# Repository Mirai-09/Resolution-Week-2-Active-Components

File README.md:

# Resolution-Week-2-Active-Components
This is a circuit that I designed for Week 2 of Resolution Hardware
My circuit has LEDs that blink when a switch is pressed as well as turn on for a few seconds and then turn off.  

# How it works
This circuit has two Multivibrators in it. The one on the left is a Astable Multivibrator. It makes the LEDs on the left blink on and off when the switch is turned on. The one on the right is a Monostable Multivibrator. When the switch on the left is pressed and released, the LEDs turn on for a few seconds and then turn off. I have made thi circuit with the help of transistors, capcitors and resistors.

# Schematic 
Here is my schematic!  

# PCB
Here is my PCB design!    
Front:  
  
Back:  
  
3D front:

3D Back:

# Demo!
GIF :)  
  
Video Link:  
https://youtu.be/-CvgjkiQHqE  
Falstad Link:  
https://is.gd/h47ZDy

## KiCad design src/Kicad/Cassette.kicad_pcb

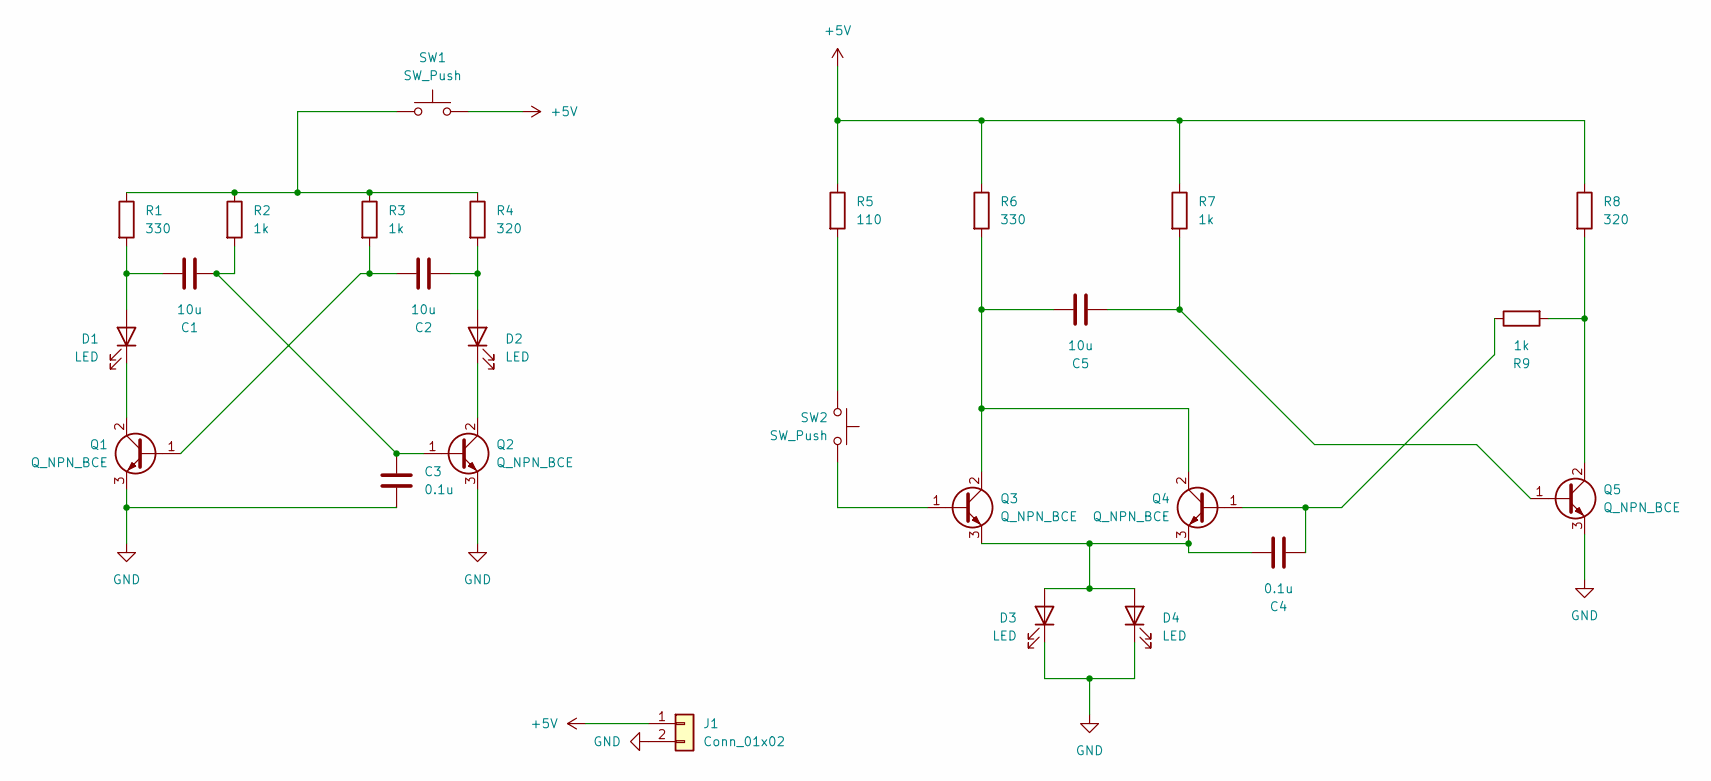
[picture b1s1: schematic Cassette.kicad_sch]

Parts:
C1, C2, C5: 10u; C_Disc_D5.0mm_W2.5mm_P5.00mm
C3, C4: 0.1u; C_Disc_D5.0mm_W2.5mm_P5.00mm
D1, D2, D3, D4: LED; LED_D5.0mm
J1: Conn_01x02; PinHeader_1x02_P2.54mm_Vertical
Q1, Q2, Q3, Q4, Q5: Q_NPN_BCE; TO-92L_Inline_Wide
R1, R6: 330; R_Axial_DIN0204_L3.6mm_D1.6mm_P7.62mm_Horizontal
R2, R3, R7, R9: 1k; R_Axial_DIN0204_L3.6mm_D1.6mm_P7.62mm_Horizontal
R4, R8: 320; R_Axial_DIN0204_L3.6mm_D1.6mm_P7.62mm_Horizontal
R5: 110; R_Axial_DIN0204_L3.6mm_D1.6mm_P7.62mm_Horizontal
SW1, SW2: SW_Push; SW_PUSH_6mm

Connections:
+5V: J1.1, R5.1, R6.1, R7.1, R8.1, SW1.2
GND: C3.2, D3.1 (K), D4.1 (K), J1.2, Q1.3 (E), Q2.3 (E), Q5.3 (E)
unnamed: C1.1, D1.2 (A), R1.2
unnamed: D1.1 (K), Q1.2 (C)
unnamed: C2.2, D2.2 (A), R4.2
unnamed: D2.1 (K), Q2.2 (C)
unnamed: C4.1, D3.2 (A), D4.2 (A), Q3.3 (E), Q4.3 (E)
unnamed: C2.1, Q1.1 (B), R3.2
unnamed: C1.2, C3.1, Q2.1 (B), R2.2
unnamed: Q3.1 (B), SW2.1
unnamed: C5.1, Q3.2 (C), Q4.2 (C), R6.2
unnamed: C4.2, Q4.1 (B), R9.1
unnamed: C5.2, Q5.1 (B), R7.2
unnamed: Q5.2 (C), R8.2, R9.2
unnamed: R1.1, R2.1, R3.1, R4.1, SW1.1
unnamed: R5.2, SW2.2

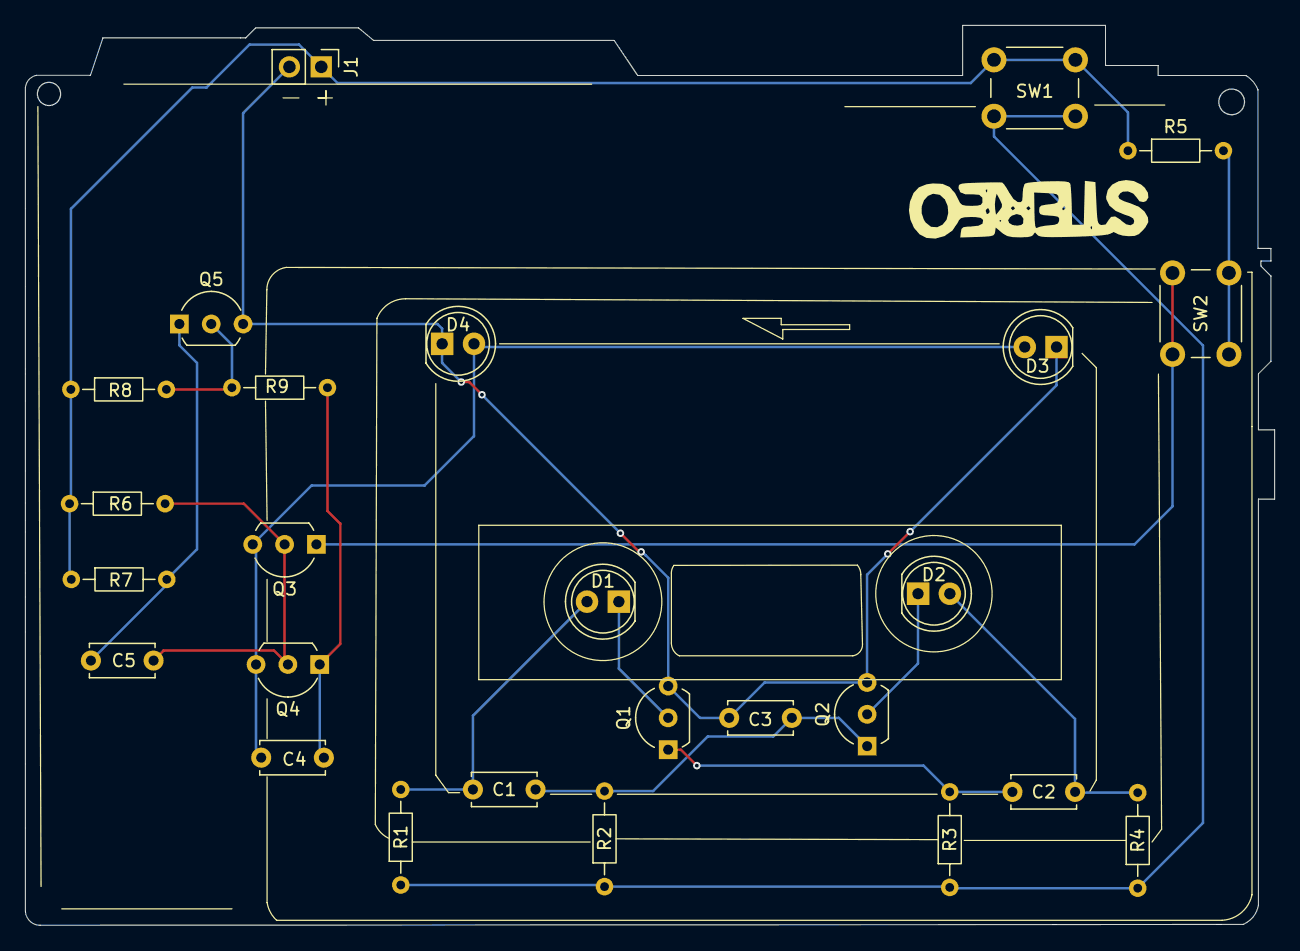
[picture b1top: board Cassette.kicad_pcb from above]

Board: 2 copper layers, 99.6 x 71.8 mm, 26 parts (0 on the bottom side), 16 nets.

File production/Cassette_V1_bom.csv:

Designator,Footprint,Quantity,Value,LCSC Part #
"C1, C2, C5",C_Disc_D5.0mm_W2.5mm_P5.00mm,3,10u,
"C3, C4",C_Disc_D5.0mm_W2.5mm_P5.00mm,2,0.1u,
"D1, D2, D3, D4",LED_D5.0mm,4,LED,
J1,PinHeader_1x02_P2.54mm_Vertical,1,Conn_01x02,
"Q1, Q2, Q3, Q4, Q5",TO-92L_Inline_Wide,5,Q_NPN_BCE,
"R1, R6",R_Axial_DIN0204_L3.6mm_D1.6mm_P7.62mm_Horizontal,2,330,
"R2, R3, R7, R9",R_Axial_DIN0204_L3.6mm_D1.6mm_P7.62mm_Horizontal,4,1k,
"R4, R8",R_Axial_DIN0204_L3.6mm_D1.6mm_P7.62mm_Horizontal,2,320,
R5,R_Axial_DIN0204_L3.6mm_D1.6mm_P7.62mm_Horizontal,1,110,
"SW1, SW2",SW_PUSH_6mm,2,SW_Push,

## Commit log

2026-03-25 Adding Cassette files
2026-03-28 Added Demo
    Added Demo GIF file
